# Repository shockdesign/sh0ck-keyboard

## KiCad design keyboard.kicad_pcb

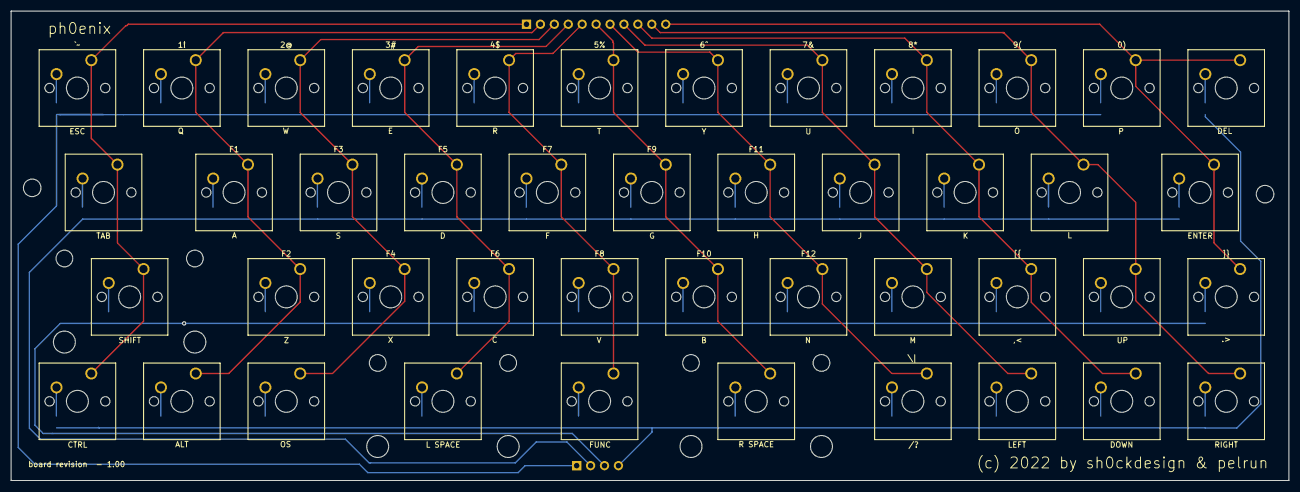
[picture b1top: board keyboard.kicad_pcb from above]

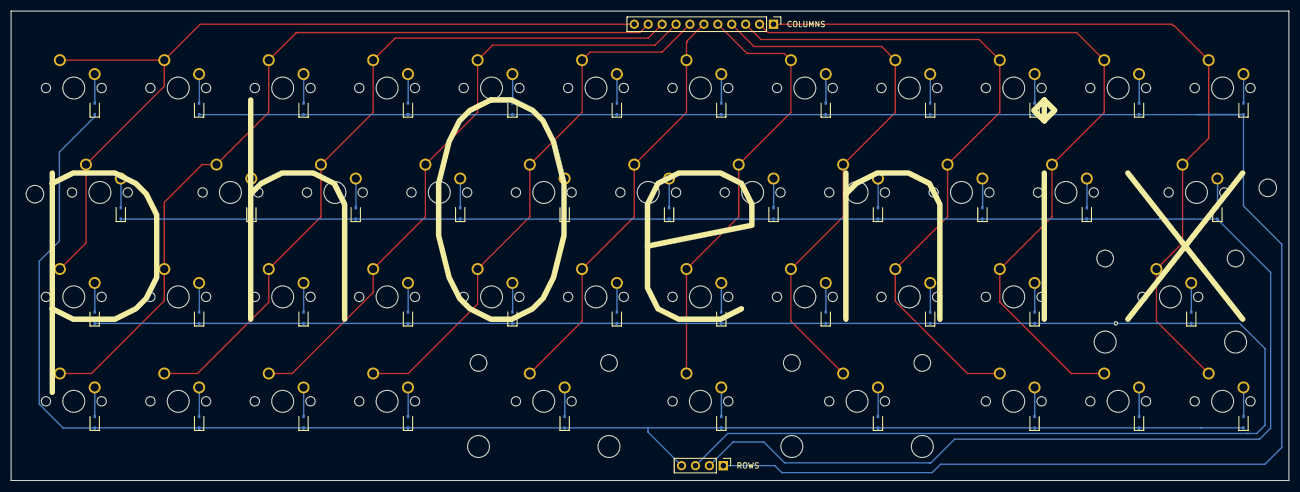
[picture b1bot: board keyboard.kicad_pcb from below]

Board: 2 copper layers, 233.1 x 85.6 mm, 92 parts (46 on the bottom side), 59 nets.

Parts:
0), 1!, 2@, 3#, 4$, 5%, 6^, 7&, 8*, 9(: KEYSW; SW_Cherry_MX_1.00u_PCB
ALT: KEYSW; SW_Cherry_MX_1.00u_PCB
COLUMNS: Conn_01x11_Male; PinHeader_1x11_P2.54mm_Vertical
CTRL: KEYSW; SW_Cherry_MX_1.00u_PCB
D1, D2, D3, D4, D5, D6, D7, D8, D9, D10, D11, D12, D13, D14, D15, D16, D17, D18, D19, D20, D21, D22, D23, D24, D25, D26, D27, D28, D29, D30, D31, D32, D33, D35, D36, D37, D38, D39, D40, D41, D42, D43: D; D_SOD-323
DEL: KEYSW; SW_Cherry_MX_1.00u_PCB
DOWN: KEYSW; SW_Cherry_MX_1.00u_PCB
ENTER: KEYSW; SW_Cherry_MX_1.50u_PCB
F1, F2, F3, F4, F5, F6, F7, F8, F9, F10, F11, F12: KEYSW; SW_Cherry_MX_1.00u_PCB
FUNC: KEYSW; SW_Cherry_MX_1.00u_PCB
H1, H2: MountingHole; MountingHole_3.2mm_M3_DIN965
J: KEYSW; SW_Cherry_MX_1.00u_PCB
K: KEYSW; SW_Cherry_MX_1.00u_PCB
L: KEYSW; SW_Cherry_MX_1.00u_PCB
L SPACE: KEYSW; SW_Cherry_MX_2.00u_PCB
LEFT: KEYSW; SW_Cherry_MX_1.00u_PCB
M: KEYSW; SW_Cherry_MX_1.00u_PCB
OS: KEYSW; SW_Cherry_MX_1.00u_PCB
R SPACE: KEYSW; SW_Cherry_MX_2.00u_PCB
RIGHT: KEYSW; SW_Cherry_MX_1.00u_PCB
ROWS: Conn_01x04_Male; PinHeader_1x04_P2.54mm_Vertical
SHIFT: KEYSW; SW_Cherry_MX_2.00u_PCB
TAB: KEYSW; SW_Cherry_MX_1.50u_PCB
UP: KEYSW; SW_Cherry_MX_1.00u_PCB
[{: KEYSW; SW_Cherry_MX_1.00u_PCB
\|: KEYSW; SW_Cherry_MX_1.00u_PCB
]}: KEYSW; SW_Cherry_MX_1.00u_PCB
`~: KEYSW; SW_Cherry_MX_1.00u_PCB
locked: D; D_SOD-323
locked#2: D; D_SOD-323

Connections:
/Col_0: COLUMNS.1, CTRL.1, SHIFT.1, TAB.1, `~.1
/Col_1: 1!.1, ALT.1, COLUMNS.2, F1.1, F2.1
/Col_2: 2@.1, COLUMNS.3, F3.1, F4.1, OS.1
/Col_3: 3#.1, COLUMNS.4, F5.1, F6.1, L SPACE.1
/Col_4: 4$.1, COLUMNS.5, F7.1, F8.1, FUNC.1
/Col_5: 5%.1, COLUMNS.6, F9.1, F10.1, R SPACE.1
/Col_6: 6^.1, COLUMNS.7, F11.1, F12.1, \|.1
/Col_7: 7&.1, COLUMNS.8, J.1, LEFT.1, M.1
/Col_8: 8*.1, COLUMNS.9, DOWN.1, K.1, [{.1
/Col_9: 9(.1, COLUMNS.10, L.1, RIGHT.1, UP.1
/Col_10: 0).1, COLUMNS.11, DEL.1, ENTER.1, ]}.1
/Row_0: D1.1 (K), D2.1 (K), D3.1 (K), D4.1 (K), D5.1 (K), D6.1 (K), D7.1 (K), D8.1 (K), D9.1 (K), D10.1 (K), ROWS.1, locked.1 (K)
/Row_1: D12.1 (K), D13.1 (K), D14.1 (K), D15.1 (K), D16.1 (K), D17.1 (K), D18.1 (K), D19.1 (K), D20.1 (K), D21.1 (K), D22.1 (K), ROWS.2
/Row_2: D23.1 (K), D24.1 (K), D25.1 (K), D26.1 (K), D27.1 (K), D28.1 (K), D29.1 (K), D30.1 (K), D31.1 (K), D32.1 (K), D33.1 (K), ROWS.3
/Row_3: D11.1 (K), D35.1 (K), D36.1 (K), D37.1 (K), D38.1 (K), D39.1 (K), D40.1 (K), D41.1 (K), D42.1 (K), D43.1 (K), ROWS.4, locked#2.1 (K)
unnamed: `~.2, locked.2 (A)
unnamed: 1!.2, D1.2 (A)
unnamed: 2@.2, D2.2 (A)
unnamed: 3#.2, D3.2 (A)
unnamed: 4$.2, D4.2 (A)
unnamed: 5%.2, D5.2 (A)
unnamed: 6^.2, D6.2 (A)
unnamed: 7&.2, D7.2 (A)
unnamed: 8*.2, D8.2 (A)
unnamed: 9(.2, D9.2 (A)
unnamed: 0).2, D10.2 (A)
unnamed: D11.2 (A), DEL.2
unnamed: D12.2 (A), TAB.2
unnamed: D13.2 (A), F1.2
unnamed: D14.2 (A), F3.2
unnamed: D15.2 (A), F5.2
unnamed: D16.2 (A), F7.2
unnamed: D17.2 (A), F9.2
unnamed: D18.2 (A), F11.2
unnamed: D19.2 (A), J.2
unnamed: D20.2 (A), K.2
unnamed: D21.2 (A), L.2
unnamed: D22.2 (A), ENTER.2
unnamed: D23.2 (A), SHIFT.2
unnamed: D24.2 (A), F2.2
unnamed: D25.2 (A), F4.2
unnamed: D26.2 (A), F6.2
unnamed: D27.2 (A), F8.2
unnamed: D28.2 (A), F10.2
unnamed: D29.2 (A), F12.2
unnamed: D30.2 (A), M.2
unnamed: D31.2 (A), [{.2
unnamed: D32.2 (A), UP.2
unnamed: D33.2 (A), ]}.2
unnamed: CTRL.2, locked#2.2 (A)
unnamed: ALT.2, D35.2 (A)
unnamed: D36.2 (A), OS.2
unnamed: D37.2 (A), L SPACE.2
unnamed: D38.2 (A), FUNC.2
unnamed: D39.2 (A), R SPACE.2
unnamed: D40.2 (A), \|.2
unnamed: D41.2 (A), LEFT.2
unnamed: D42.2 (A), DOWN.2
unnamed: D43.2 (A), RIGHT.2

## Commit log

2022-03-12 No microchip, keep it basic
2022-03-12 Added a bit of text
2022-03-13 And reroute a few things, smaller board
2022-03-13 Moar changes
2022-03-14 Generated gerbers
2022-03-17 Reroute board, better silkscreening and added images
2022-03-17 Copy board to make a hotswap version
2022-03-17 Updated gerbers
2022-03-17 Updated zip for gerbers
2022-03-23 Ignore backups directory
2022-05-19 Added firmware to repo
2022-05-24 Fix bad import issue and add diode-orientation
2022-06-09 Updated firmware to now include missing keys and proper escape
2022-06-17 Now with pico
2022-06-21 Added new board, and firmware to match
2022-06-21 Minor position change on the Phoenix graphic and removal of D5 text
2022-06-21 Update r1.01 with gerbers for production
2022-07-20 Updated board and firmware with new routing, makes sure the Pi Pico is facing the right way
2022-07-23 Updated v1.01 and ready for production

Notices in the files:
keyboard.kicad_pcb:
(c) 2022 by sh0ckdesign & pelrun
